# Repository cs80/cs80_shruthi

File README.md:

# cs80_shruthi
Eagle sch and brd for shruthi cs80 filter
These are xml format, Eagle 6.0 or greater
required.

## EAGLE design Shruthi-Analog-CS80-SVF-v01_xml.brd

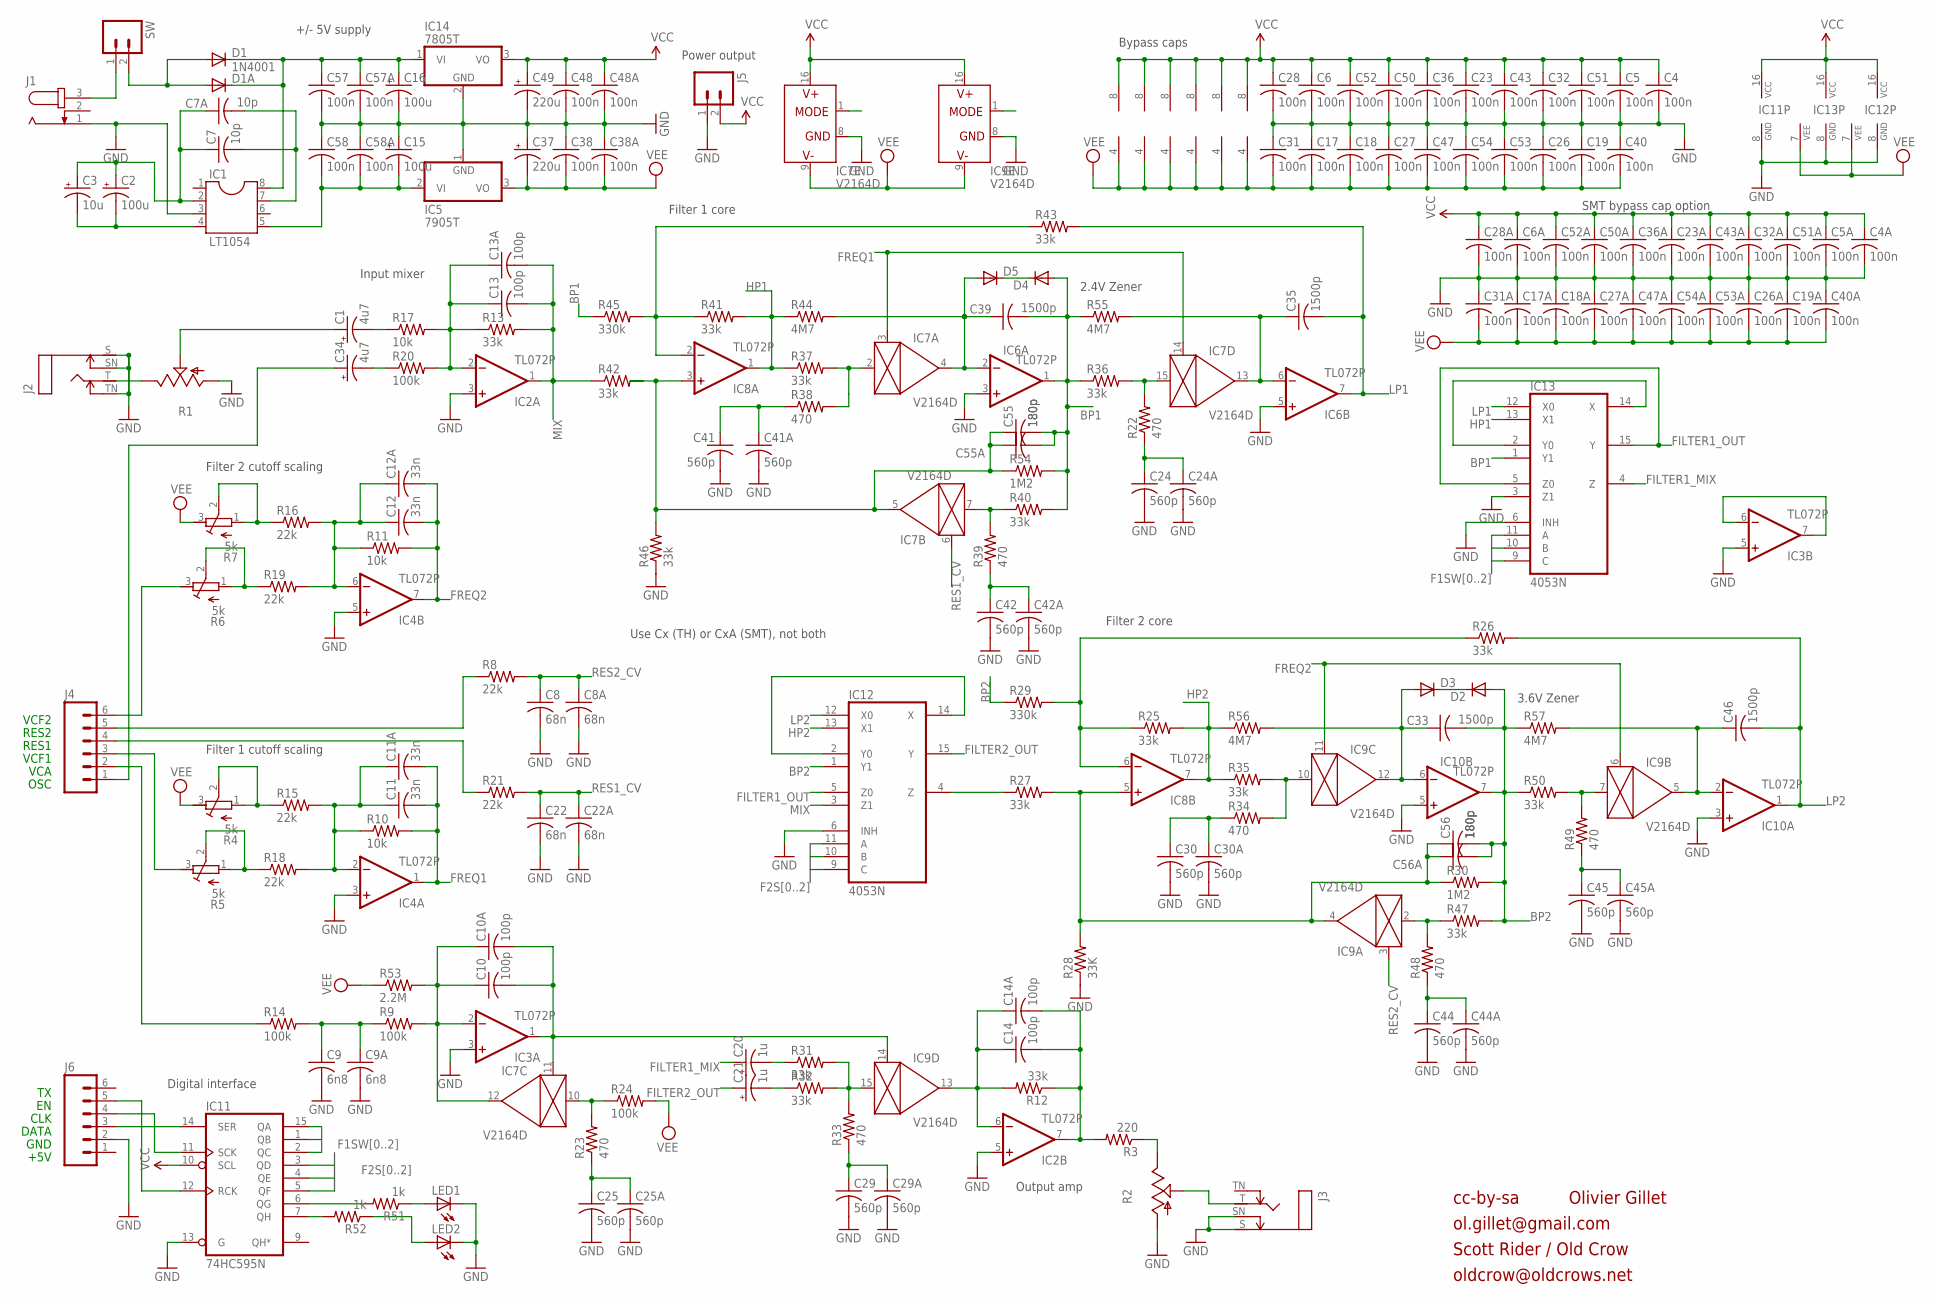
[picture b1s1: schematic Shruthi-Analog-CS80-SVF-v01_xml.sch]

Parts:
C1, C34: 4u7; E2,5-6
C2: 100u; E2,5-6
C3: 10u; E2,5-5
C4, C5, C6, C17, C18, C19, C23, C26, C27, C28, C31, C32, C36, C38, C40, C43, C47, C48, C50, C51, C52, C54, C57, C58: 100n; C050-025X075
C4A, C5A, C6A, C17A, C18A, C19A, C23A, C26A, C27A, C28A, C31A, C32A, C36A, C38A, C40A, C43A, C47A, C48A, C50A, C51A, C52A, C53A, C54A, C57A, C58A: 100n; C0805K
C7: 10p; C050-025X075
C7A: 10p; C0805K
C8, C22: 68n; C050-025X075
C8A, C22A: 68n; C0805K
C9: 6n8; C050-025X075
C9A: 6n8; C0805K
C10, C13, C14: 100p; C050-025X075
C10A, C13A, C14A: 100p; C0805K
C11, C12: 33n; C050-025X075
C11A, C12A: 33n; C0805K
C15, C16: 100u; E2,5-7
C20, C21: 1u; E2-5
C24, C25, C29, C30, C41, C42, C44, C45: 560p; C050-025X075
C24A, C25A, C29A, C30A, C41A, C42A, C44A, C45A: 560p; C0805K
C33, C35, C39, C46: 1500p; C025-025X050
C37, C49: 220u; E3,5-8
C53: 100n; C025-025X050
C55, C56: 180p; C050-025X075
C55A, C56A: 180p; C0805K
D1: 1N4001; DO41-10
D1A: DIODE-SMB; SMB
D2, D3, D4, D5: DIODE-D-5; D-5
IC1: LT1054; DIL08
IC2, IC3, IC4, IC6, IC8, IC10: TL072P; DIL08
IC5: 7905T; TO220H
IC7, IC9: V2164D; DIL16
IC11: 74HC595N; DIL16
IC12, IC13: 4053N; DIL16
IC14: 7805T; TO220H
J1: JACK-PLUG2; SPC4078_BIG_HOLES
J2, J3: MONOSWS; NMJ4HC-S
J4, J6: M06SIP; 1X06
J5: M02PTH; 1X02
LED1, LED2: LEDCHIP-LED0603; CHIP-LED0603
R1, R2: POT_USCABLED; CABLE_POT_6MM
R3: 220; 0204/7
R4, R5, R6, R7: 5k; RTRIM3296X
R8, R15, R16, R18, R19, R21: 22k; 0204/7
R9, R14, R20, R24: 100k; 0204/7
R10, R11, R17: 10k; 0204/7
R12, R13, R25, R26, R27, R31, R32, R35, R36, R37, R40, R41, R42, R43, R46, R47, R50: 33k; 0204/7
R22, R23, R33, R34, R38, R39, R48, R49: 470; 0204/7
R28: 33K; 0204/7
R29, R45: 330k; 0204/7
R30, R54: 1M2; 0204/7
R44, R55, R56, R57: 4M7; 0204/7
R51, R52: 1k; 0204/7
R53: 2.2M; 0204V
SW: M02PTH; 1X02

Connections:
BP1: C39.2, C55.2, C55A.2, D4.A, IC6.1 (OUT), IC13.1 (Y1), R36.1, R40.2, R45.1, R54.2, R55.1
BP2: C33.2, C56.2, C56A.2, D2.A, IC10.7 (OUT), IC12.1 (Y1), R29.1, R30.2, R47.2, R50.1, R57.1
F1SW0: IC11.15 (QA), IC13.9 (C)
F1SW1: IC11.1 (QB), IC13.10 (B)
F1SW2: IC11.2 (QC), IC13.11 (A)
F2S0: IC11.3 (QD), IC12.9 (C)
F2S1: IC11.4 (QE), IC12.10 (B)
F2S2: IC11.5 (QF), IC12.11 (A)
FILTER1_MIX: C20.+, IC13.4 (Z)
FILTER1_OUT: IC12.5 (Z0), IC13.5 (Z0), IC13.15 (Y)
FILTER2_OUT: C21.+, IC12.15 (Y)
FREQ1: C11.2, C11A.2, IC4.1 (OUT), IC7.3 (CTRL), IC7.14 (CTRL), R10.2
FREQ2: C12.2, C12A.2, IC4.7 (OUT), IC9.6 (CTRL), IC9.11 (CTRL), R11.2
GND: C4.2, C4A.2, C5.2, C5A.2, C6.2, C6A.2, C8.2, C8A.2, C9.2, C9A.2, C15.+, C16.-, C17.1, C17A.1, C18.1, C18A.1, C19.1, C19A.1, C22.2, C22A.2, C23.2, C23A.2, C24.2, C24A.2, C25.2, C25A.2, C26.1, C26A.1, C27.1, C27A.1, C28.2, C28A.2, C29.2, C29A.2, C30.2, C30A.2, C31.1, C31A.1, C32.2, C32A.2, C36.2, C36A.2, C37.+, C38.1, C38A.1, C40.1, C40A.1, C41.2, C41A.2, C42.2, C42A.2, C43.2, C43A.2, C44.2, C44A.2, C45.2, C45A.2, C47.1, C47A.1, C48.2, C48A.2, C49.-, C50.2, C50A.2, C51.2, C51A.2, C52.2, C52A.2, C53.1, C53A.1, C54.1, C54A.1, C57.2, C57A.2, C58.1, C58A.1, IC1.3, IC2.3 (+IN), IC2.5 (+IN), IC3.3 (+IN), IC3.5 (+IN), IC4.3 (+IN), IC4.5 (+IN), IC5.1 (GND), IC6.3 (+IN), IC6.5 (+IN), IC7.8 (GND), IC9.8 (GND), IC10.3 (+IN), IC10.5 (+IN), IC11.8 (GND), IC11.13 (G), IC12.6 (INH), IC12.8 (GND), IC13.3 (Z1), IC13.6 (INH), IC13.8 (GND), IC14.2 (GND), J1.1, J2.S, J2.SN, J2.TN, J3.S, J3.SN, J5.1, J6.2, LED1.C, LED2.C, R1.A, R2.A, R28.1, R46.1
HP1: IC8.1 (OUT), IC13.13 (X1), R37.1, R41.2, R44.1
HP2: IC8.7 (OUT), IC12.13 (X1), R25.2, R35.1, R56.1
LP1: C35.2, IC6.7 (OUT), IC13.12 (X0), R43.2
LP2: C46.2, IC10.1 (OUT), IC12.12 (X0), R26.2
MIX: C13.2, C13A.2, IC2.1 (OUT), IC12.3 (Z1), R13.2, R42.1
unnamed: C2.+, C3.+, C7.1, C7A.1, IC1.2
unnamed: C12.1, C12A.1, IC4.6 (-IN), R11.1, R16.2, R19.2
unnamed: J1.3, SW.1
unnamed: C16.+, C57.1, C57A.1, D1.C, D1A.C, IC1.8, IC14.1 (VI)
unnamed: C2.-, C3.-, IC1.4
unnamed: C13.1, C13A.1, IC2.2 (-IN), R13.1, R17.2, R20.2
unnamed: R6.1 (E), R6.2 (S), R19.1
unnamed: J4.6, R6.3 (A)
unnamed: R7.1 (E), R7.2 (S), R16.1
unnamed: IC7.10 (IN), R23.2, R24.1
unnamed: C10.1, C10A.1, IC3.2 (-IN), IC7.12 (OUT), R9.2, R53.2
unnamed: IC8.2 (-IN), R41.1, R43.1, R45.2
unnamed: IC11.12 (RCK), J6.5
unnamed: IC11.14 (SER), J6.3
unnamed: IC11.6 (QG), R51.2
unnamed: IC11.11 (SCK), J6.4
unnamed: C24.1, C24A.1, R22.1
unnamed: IC8.6 (-IN), R25.1, R26.1, R29.2
unnamed: C39.1, D5.A, IC6.2 (-IN), IC7.4 (OUT), R44.2
unnamed: C33.1, D3.A, IC9.12 (OUT), IC10.6 (-IN), R56.2
unnamed: IC7.7 (IN), R39.2, R40.1
unnamed: C9.1, C9A.1, R9.1, R14.2
unnamed: C56.1, C56A.1, IC8.5 (+IN), IC9.4 (OUT), R27.2, R28.2, R30.1
unnamed: IC9.2 (IN), R47.1, R48.2
unnamed: R2.E, R3.1
unnamed: IC7.15 (IN), R22.2, R36.2
unnamed: C42.1, C42A.1, R39.1
unnamed: C35.1, IC6.6 (-IN), IC7.13 (OUT), R55.2
unnamed: IC7.2 (IN), R37.2, R38.2
unnamed: C41.1, C41A.1, R38.1
unnamed: C55.1, C55A.1, IC7.5 (OUT), IC8.3 (+IN), R42.2, R46.2, R54.1
unnamed: LED1.A, R51.1
unnamed: D2.C, D3.C
unnamed: IC9.7 (IN), R49.2, R50.2
unnamed: C34.+, J4.1
unnamed: C7.2, C7A.2, IC1.7
unnamed: J2.T, R1.E
unnamed: C34.-, R20.1
unnamed: C11.1, C11A.1, IC4.2 (-IN), R10.1, R15.2, R18.2
unnamed: R5.1 (E), R5.2 (S), R18.1
unnamed: J4.3, R5.3 (A)
unnamed: R4.1 (E), R4.2 (S), R15.1
unnamed: C46.1, IC9.5 (OUT), IC10.2 (-IN), R57.2
unnamed: J4.2, R14.1
unnamed: C45.1, C45A.1, R49.1
unnamed: J3.T, R2.S
unnamed: C44.1, C44A.1, R48.1
unnamed: IC9.10 (IN), R34.2, R35.2
unnamed: C30.1, C30A.1, R34.1
unnamed: LED2.A, R52.1
unnamed: IC11.7 (QH), R52.2
unnamed: D4.C, D5.C
unnamed: C10.2, C10A.2, IC3.1 (OUT), IC7.11 (CTRL), IC9.14 (CTRL)
unnamed: C20.-, R31.1
unnamed: C15.-, C58.2, C58A.2, IC1.5, IC5.2 (VI)
unnamed: D1.A, D1A.A, SW.2
unnamed: C21.-, R32.1
unnamed: IC3.6 (-IN), IC3.7 (OUT)
unnamed: IC13.2 (Y0), IC13.14 (X)
unnamed: C14.2, C14A.2, IC2.7 (OUT), R3.2, R12.1
unnamed: C25.1, C25A.1, R23.1
unnamed: C29.1, C29A.1, R33.1
unnamed: C1.+, R1.S
unnamed: IC9.15 (IN), R31.2, R32.2, R33.2
unnamed: J4.4, R21.1
unnamed: C14.1, C14A.1, IC2.6 (-IN), IC9.13 (OUT), R12.2
unnamed: C1.-, R17.1
unnamed: J4.5, R8.1
unnamed: IC12.2 (Y0), IC12.14 (X)
unnamed: IC12.4 (Z), R27.1
RES1_CV: C22.1, C22A.1, IC7.6 (CTRL), R21.2
RES2_CV: C8.1, C8A.1, IC9.3 (CTRL), R8.2
VCC: C4.1, C4A.1, C5.1, C5A.1, C6.1, C6A.1, C23.1, C23A.1, C28.1, C28A.1, C32.1, C32A.1, C36.1, C36A.1, C43.1, C43A.1, C48.1, C48A.1, C49.+, C50.1, C50A.1, C51.1, C51A.1, C52.1, C52A.1, IC2.8 (V+), IC3.8 (V+), IC4.8 (V+), IC6.8 (V+), IC7.16 (V+), IC8.8 (V+), IC9.16 (V+), IC10.8 (V+), IC11.10 (SCL), IC11.16 (VCC), IC12.16 (VCC), IC13.16 (VCC), IC14.3 (VO), J5.2
VEE: C17.2, C17A.2, C18.2, C18A.2, C19.2, C19A.2, C26.2, C26A.2, C27.2, C27A.2, C31.2, C31A.2, C37.-, C38.2, C38A.2, C40.2, C40A.2, C47.2, C47A.2, C53.2, C53A.2, C54.2, C54A.2, IC2.4 (V-), IC3.4 (V-), IC4.4 (V-), IC5.3 (VO), IC6.4 (V-), IC7.9 (V-), IC8.4 (V-), IC9.9 (V-), IC10.4 (V-), IC12.7 (VEE), IC13.7 (VEE), R4.3 (A), R7.3 (A), R24.2, R53.1

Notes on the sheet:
Power output
OSC
VCA
VCF1
RES1
Input mixer
Filter 1 cutoff scaling
cc-by-sa
Olivier Gillet
ol.gillet@gmail.com
+/- 5V supply
Bypass caps
Output amp
VCF2
RES2
+5V
GND
DATA
CLK
Digital interface
Filter 2 cutoff scaling
Filter 1 core
Filter 2 core
3.6V Zener
2.4V Zener
SMT bypass cap option
Use Cx (TH) or CxA (SMT), not both
Scott Rider / Old Crow
oldcrow@oldcrows.net

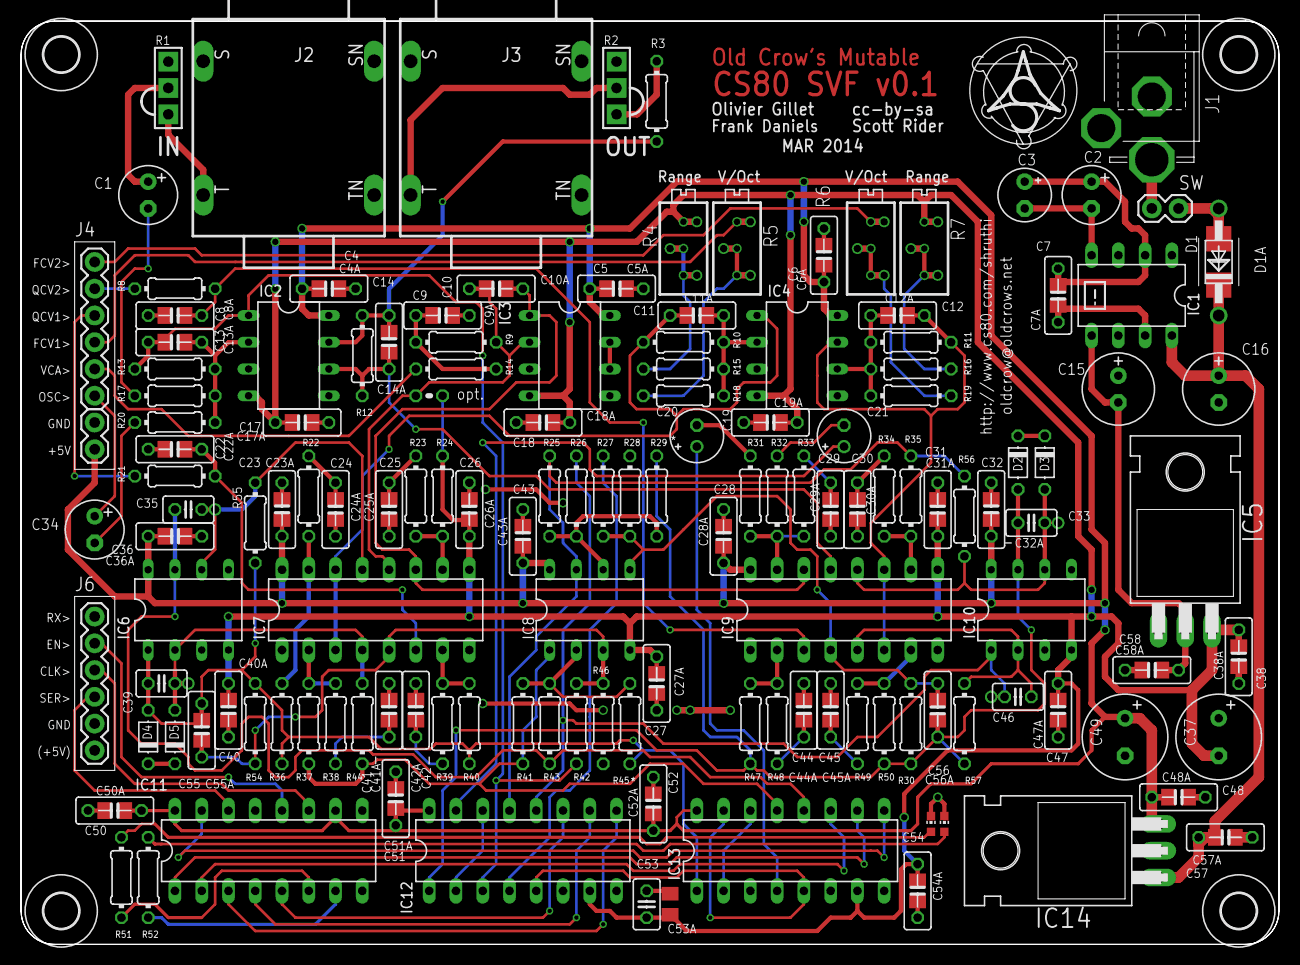
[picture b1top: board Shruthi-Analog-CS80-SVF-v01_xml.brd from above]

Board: 4 copper layers, 119.4 x 87.6 mm, 192 parts (0 on the bottom side), 93 nets.

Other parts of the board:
U$1, U$2, U$3, U$4: 3,3

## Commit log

2016-01-13 :boom::camel: Added .gitattributes & .gitignore files
2016-01-13 README.md
2016-01-13 Added sch & brd for sc80 shruthi filter
2016-01-13 Made sure XML Eagle CAD files in repo
2016-01-13 Added pdfs
